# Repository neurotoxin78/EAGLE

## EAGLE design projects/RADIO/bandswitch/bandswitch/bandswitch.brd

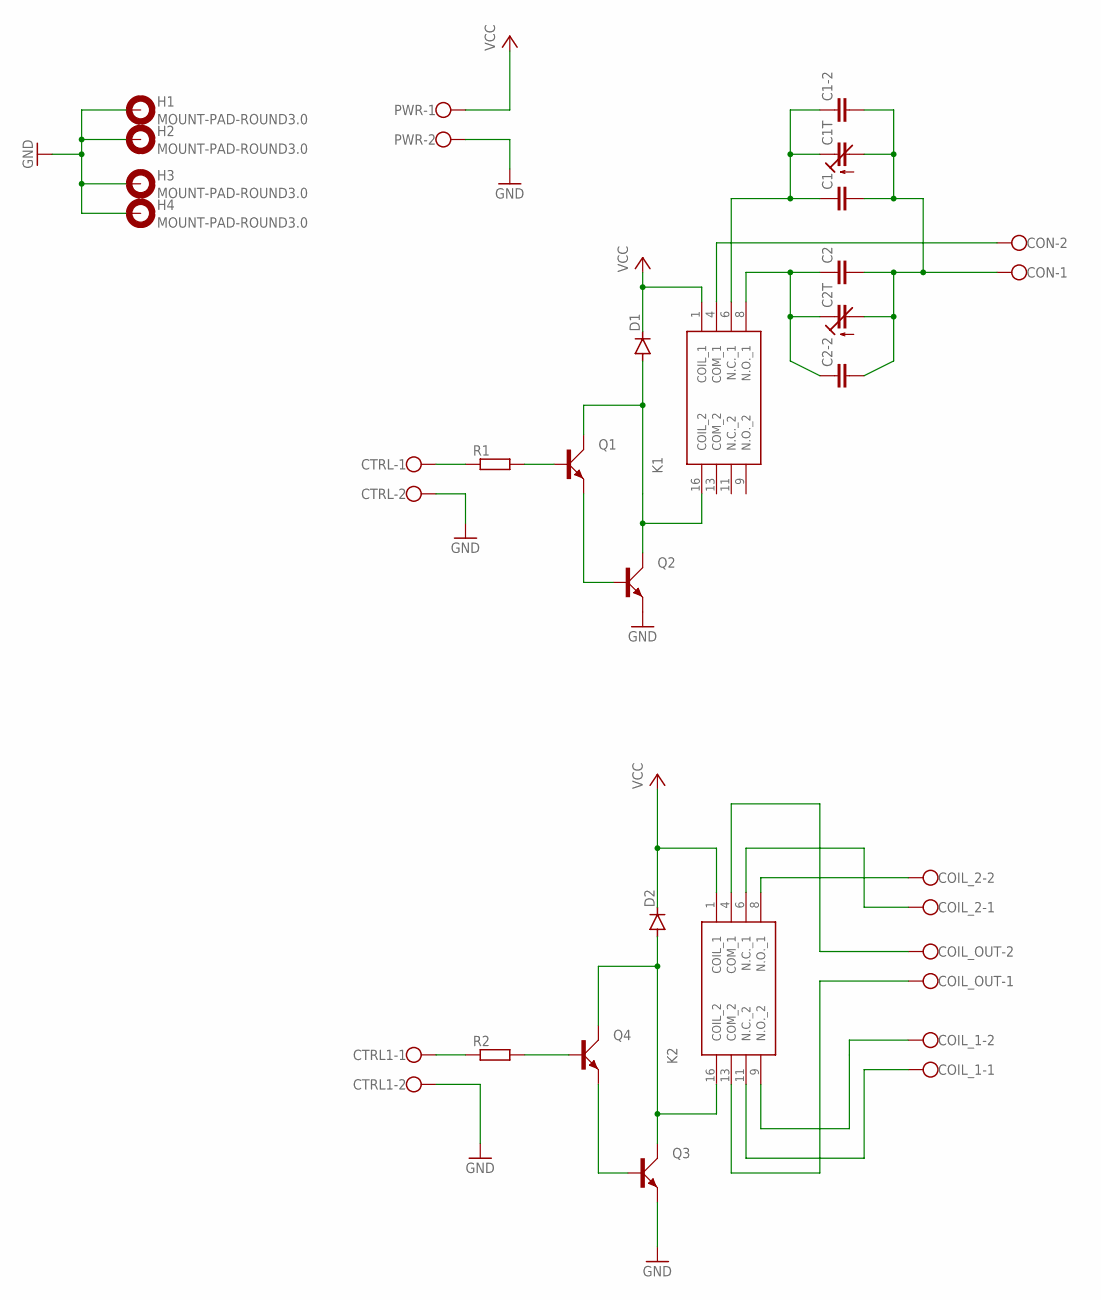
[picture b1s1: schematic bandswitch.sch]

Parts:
C1, C1-2, C2, C2-2: C_0805_PTH; C0805K
C1T, C2T: C_TRIM_TH; CTRIM3050.505
COIL_1, COIL_2: W237-102
COIL_OUT: W237-102
CON: W237-102
CTRL, CTRL1: W237-102
D1, D2: 1N4148DO35-7; DO35-7
H1, H2, H3, H4: MOUNT-PAD-ROUND3.0; 3,0-PAD
K1, K2: G5V-2-H1-DC5; G5V2H1DC5
PWR: W237-102
Q1, Q2, Q3, Q4: BC547; SOT54A
R1, R2: R_0805_PTH; R0805

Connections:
GND: CTRL.2, CTRL1.2, H1.B3,0, H2.B3,0, H3.B3,0, H4.B3,0, PWR.2, Q2.E, Q3.E
unnamed: Q1.E, Q2.B
unnamed: D1.A, K1.16 (COIL_2), Q1.C, Q2.C
unnamed: Q1.B, R1.2, R1.P$2 (2)
unnamed: CTRL.1, R1.1, R1.P$1 (1)
unnamed: D2.A, K2.16 (COIL_2), Q3.C, Q4.C
unnamed: Q3.B, Q4.E
unnamed: Q4.B, R2.2, R2.P$2 (2)
unnamed: CTRL1.1, R2.1, R2.P$1 (1)
unnamed: COIL_OUT.2, K2.4 (COM_1)
unnamed: C1.1, C1.P$1 (1), C1-2.1, C1-2.P$1 (1), C1T.2 (E), K1.6 (N.C._1)
unnamed: C2.1, C2.P$1 (1), C2-2.1, C2-2.P$1 (1), C2T.2 (E), K1.8 (N.O._1)
unnamed: C1.2, C1.P$2 (2), C1-2.2, C1-2.P$2 (2), C1T.1 (A), C2.2, C2.P$2 (2), C2-2.2, C2-2.P$2 (2), C2T.1 (A), CON.1
unnamed: CON.2, K1.4 (COM_1)
unnamed: COIL_OUT.1, K2.13 (COM_2)
unnamed: COIL_1.1, K2.11 (N.C._2)
unnamed: COIL_2.1, K2.6 (N.C._1)
unnamed: COIL_2.2, K2.8 (N.O._1)
unnamed: COIL_1.2, K2.9 (N.O._2)
VCC: D1.C, D2.C, K1.1 (COIL_1), K2.1 (COIL_1), PWR.1

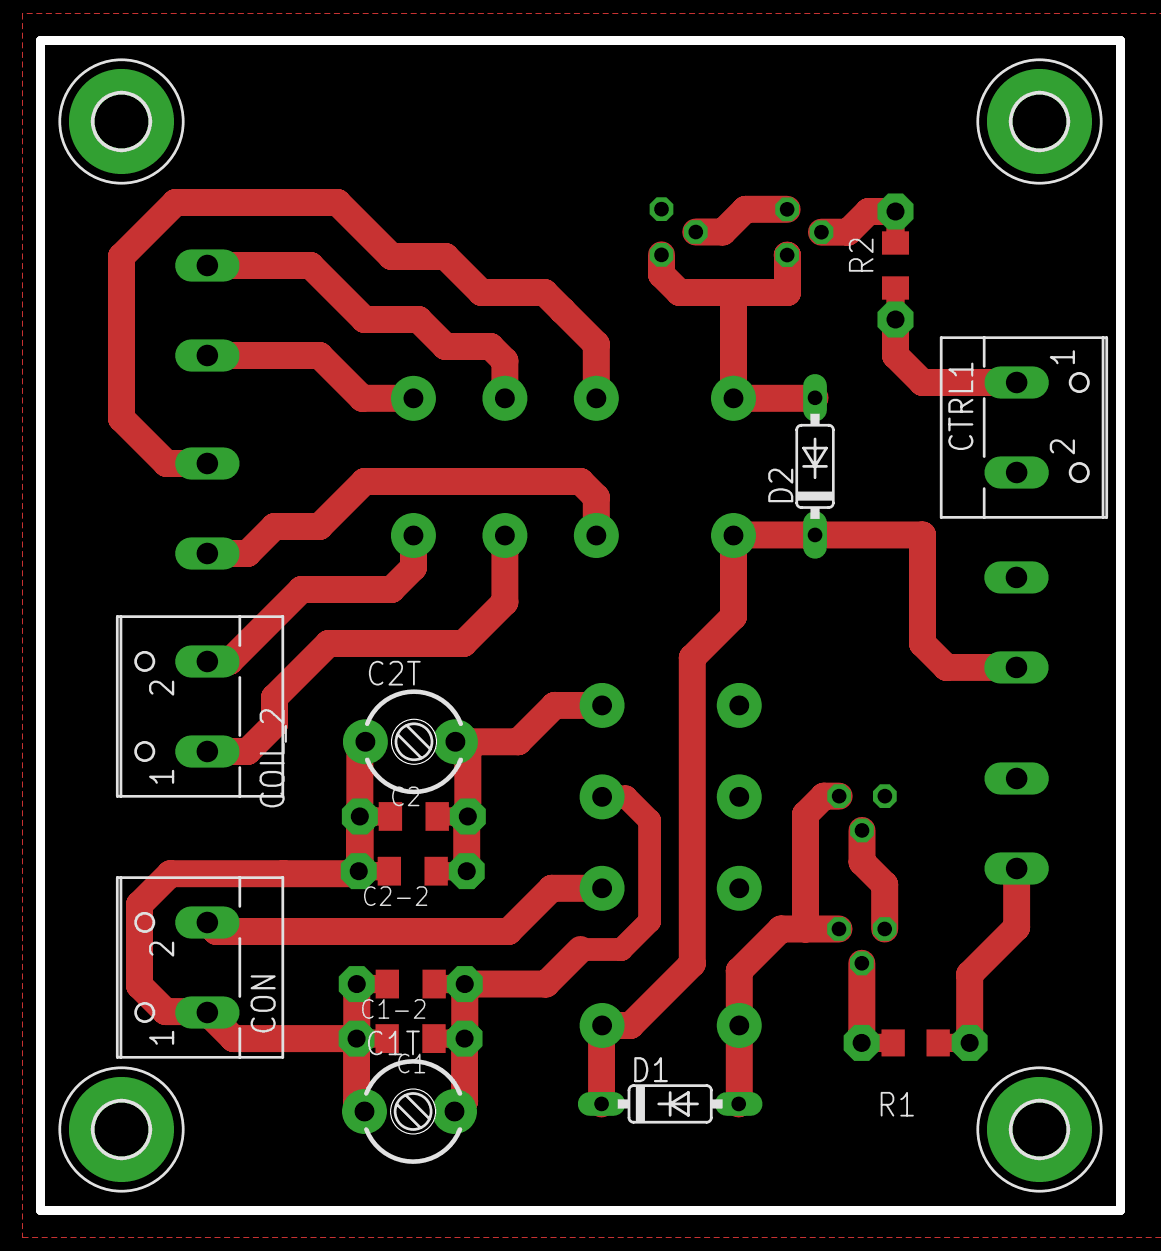
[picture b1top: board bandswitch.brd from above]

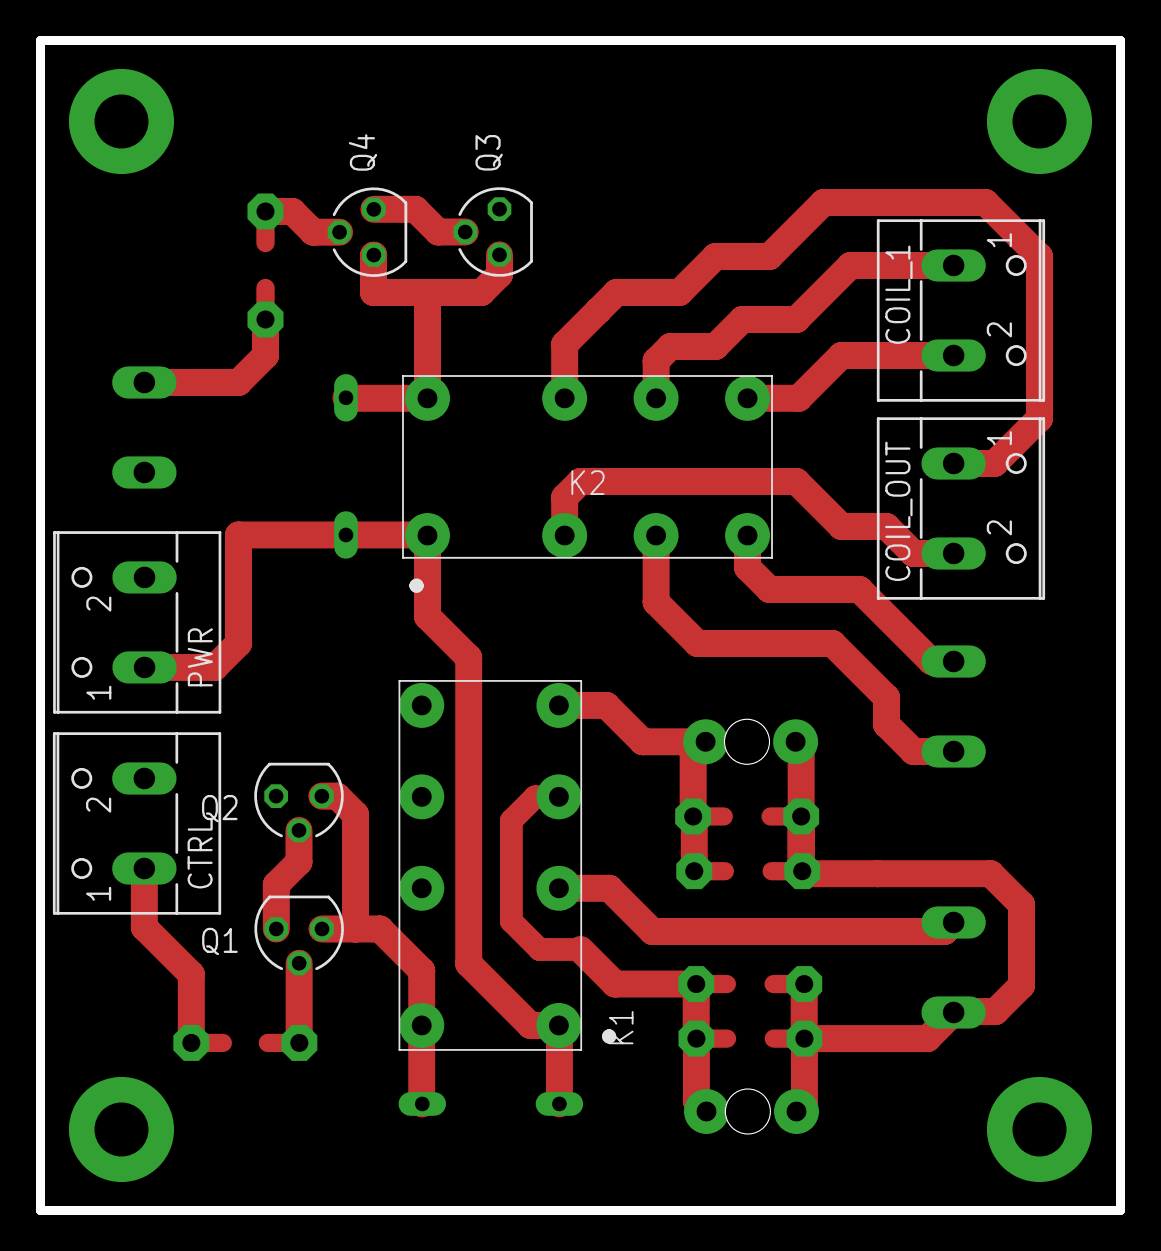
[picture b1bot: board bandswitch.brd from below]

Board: 2 copper layers, 60.0 x 65.0 mm, 27 parts (10 on the bottom side), 20 nets.

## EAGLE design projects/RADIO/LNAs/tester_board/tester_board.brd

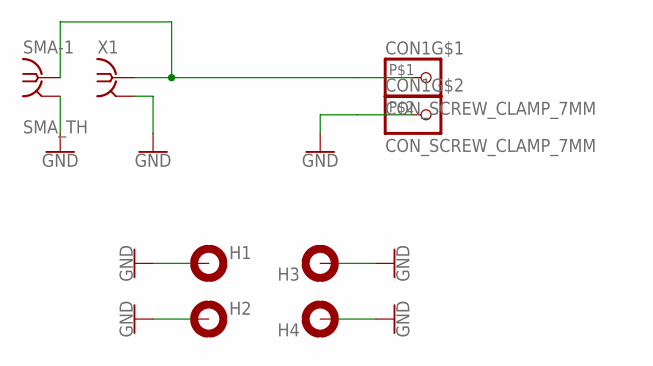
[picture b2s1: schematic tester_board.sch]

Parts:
CON1: CON_SCREW_CLAMP_7MM
H1, H2, H3, H4: MOUNT-PAD-ROUND3.0; 3,0-PAD
SMA-1: SMA_TH; BU-SMA-V
X1: SMA-142-0711-821/826; J502-ND-142-0711-821/826

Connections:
GND: CON1.P$2, H1.B3,0, H2.B3,0, H3.B3,0, H4.B3,0, SMA-1.2 (GND), SMA-1.3 (GND), SMA-1.4 (GND), SMA-1.5 (GND), X1.G@1 (2), X1.G@2 (2), X1.G@3 (2), X1.G@4 (2)
unnamed: CON1.P$1, SMA-1.1, X1.1

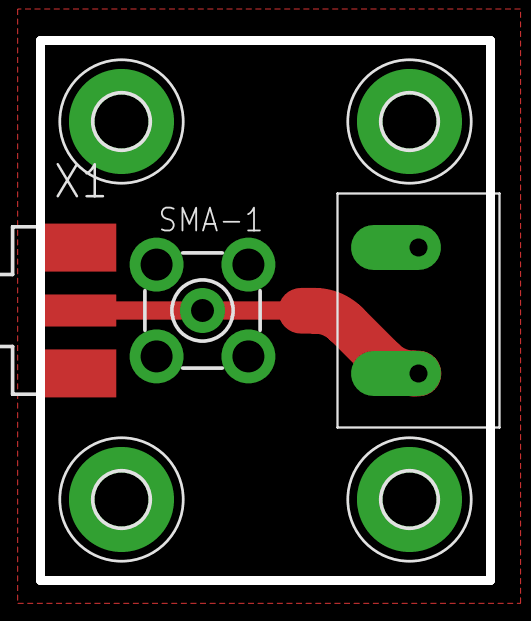
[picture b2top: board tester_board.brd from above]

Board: 2 copper layers, 25.0 x 30.0 mm, 7 parts (0 on the bottom side), 2 nets.

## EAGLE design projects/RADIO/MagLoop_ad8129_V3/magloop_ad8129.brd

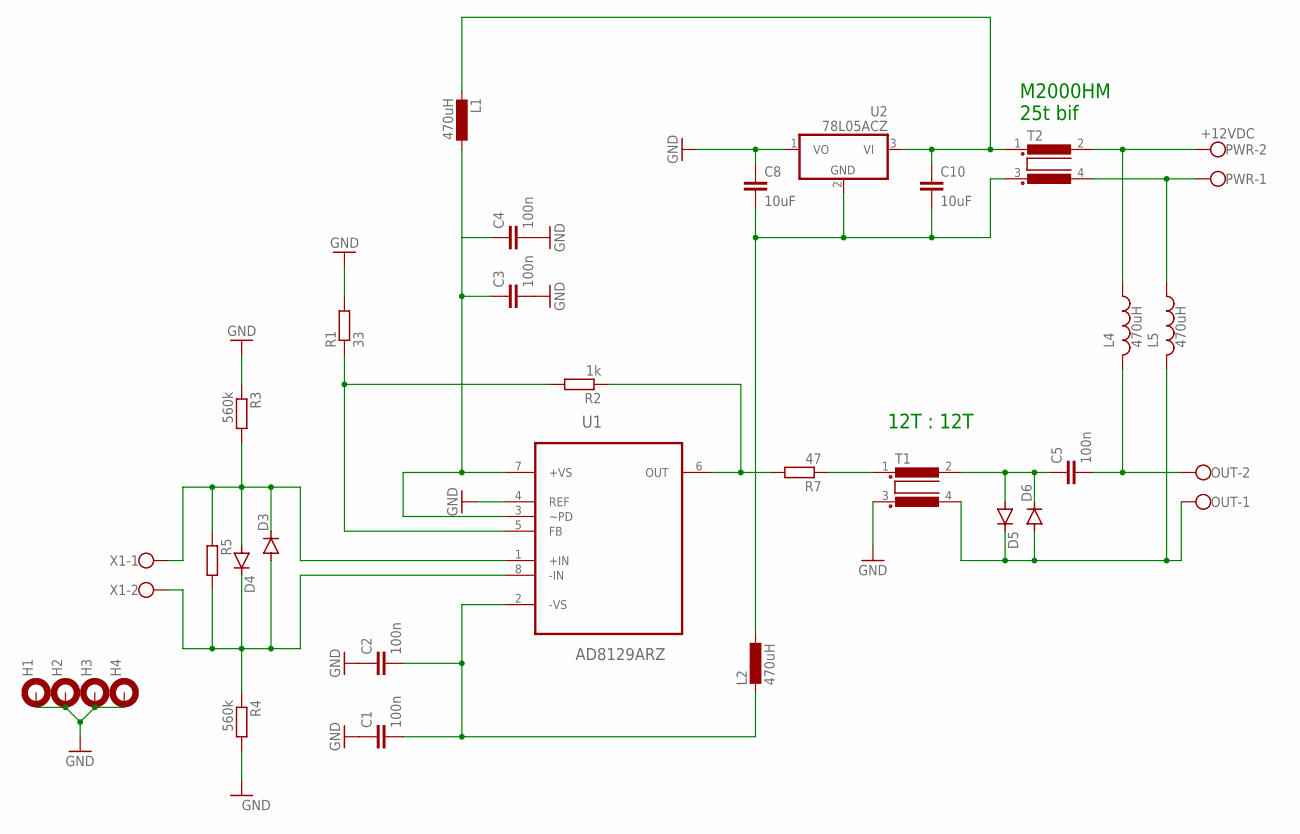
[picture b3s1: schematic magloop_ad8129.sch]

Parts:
C1, C2, C3, C4: 100n; C0805
C5: 100n; C0805K
C8, C10: 10uF; C1206K
D3, D4: LL4148; SOD-123_MINI-SMA
D5, D6: CGRM4001-G; SOD-123_MINI-SMA
H1, H2, H3, H4: MOUNT-PAD-ROUND3.0; 3,0-PAD
L1, L2: 470uH; 0207/10
L4, L5: 470uH; M0805
OUT: W237-102
PWR: +12VDC; W237-102
R1: 33; R0805W
R2: 1k; R0805W
R3, R4: 560k; R0805
R5: R_0805_PTH; R0805
R7: 47; R1206
T1, T2: R1405UB1/2; B1/2
U1: AD8129ARZ; SOIC127P600X175-8N
U2: 78L05ACZ; TO-92
X1: W237-102

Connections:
GND: C1.1, C2.1, C3.2, C4.2, C8.1, H1.B3,0, H2.B3,0, H3.B3,0, H4.B3,0, R1.2, R3.1, R3.P$1 (1), R4.2, R4.P$2 (2), T1.3, U1.4 (REF), U2.1 (VO)
unnamed: D3.C, D4.A, R3.2, R3.P$2 (2), R5.1, R5.P$1 (1), U1.1 (+IN), X1.1
unnamed: D3.A, D4.C, R4.1, R4.P$1 (1), R5.2, R5.P$2 (2), U1.8 (-IN), X1.2
unnamed: R1.1, R2.2, U1.5 (FB)
unnamed: R2.1, R7.2, U1.6 (OUT)
unnamed: C3.1, C4.1, L1.1, U1.3 (~PD), U1.7 (+VS)
unnamed: C10.1, L1.2, T2.1, U2.3 (VI)
unnamed: C8.2, C10.2, L2.1, T2.3, U2.2 (GND)
unnamed: L5.1, L5.P$1 (1), PWR.1, T2.4
unnamed: L4.1, L4.P$1 (1), PWR.2, T2.2
unnamed: C1.2, C2.2, L2.2, U1.2 (-VS)
unnamed: R7.1, T1.1
unnamed: C5.1, C5.P$1 (1), D5.A, D6.C, T1.2
unnamed: C5.2, C5.P$2 (2), L4.2, L4.P$2 (2), OUT.2
unnamed: D5.C, D6.A, L5.2, L5.P$2 (2), OUT.1, T1.4

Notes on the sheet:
12T : 12T
M2000HM 25t bif

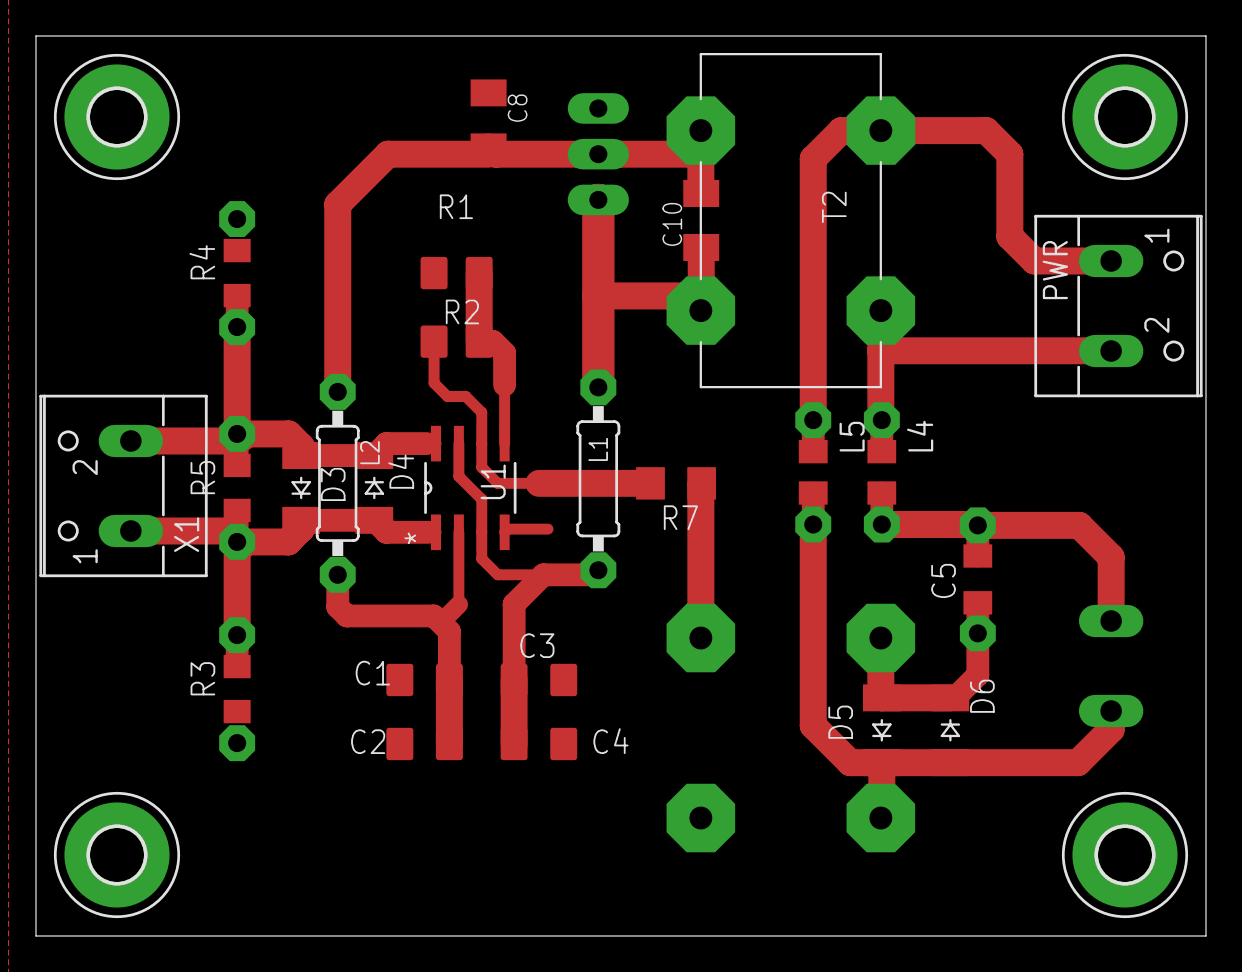
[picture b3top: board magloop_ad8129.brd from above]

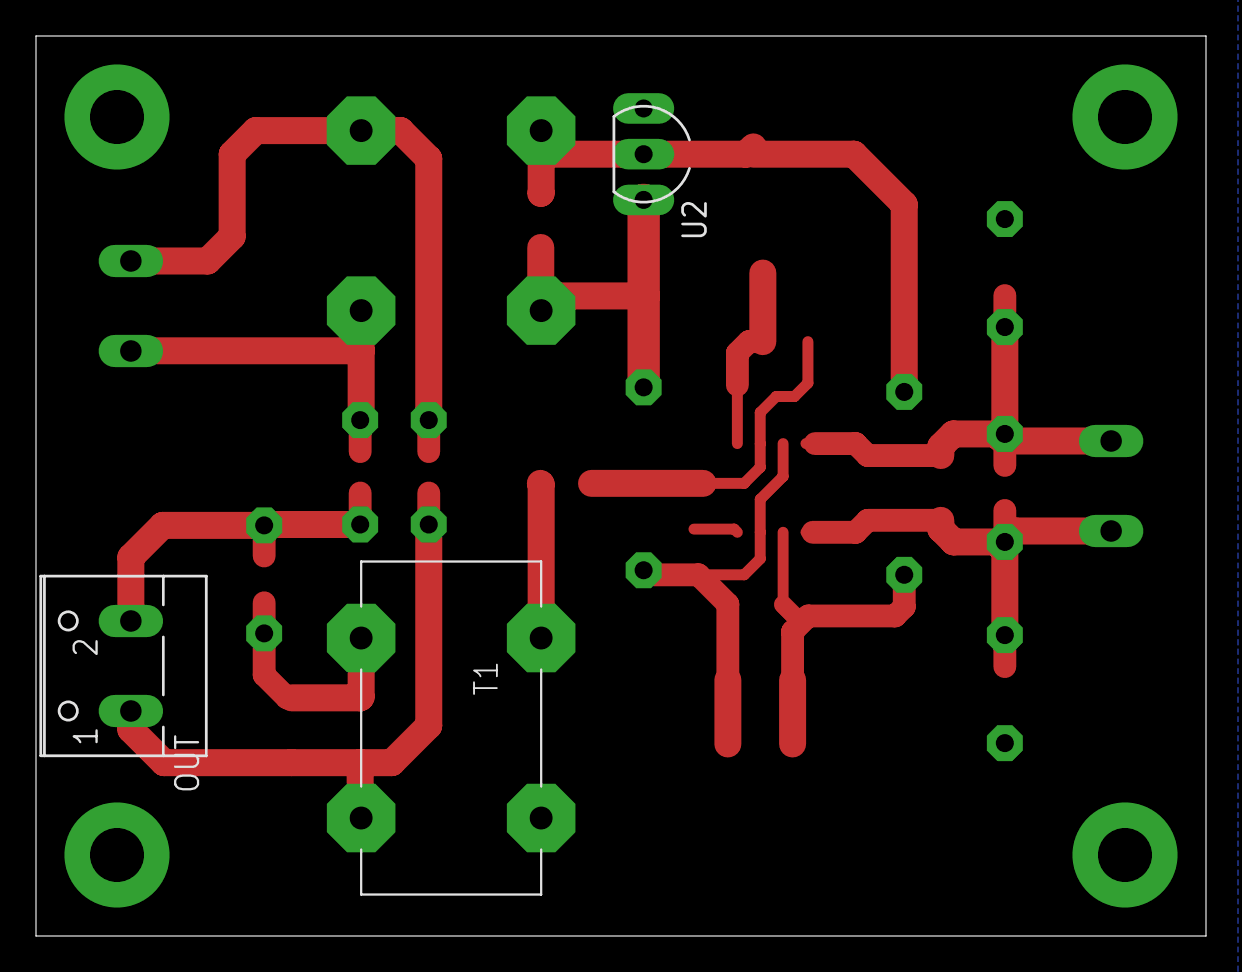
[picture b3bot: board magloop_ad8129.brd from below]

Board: 2 copper layers, 65.0 x 50.0 mm, 32 parts (3 on the bottom side), 15 nets.

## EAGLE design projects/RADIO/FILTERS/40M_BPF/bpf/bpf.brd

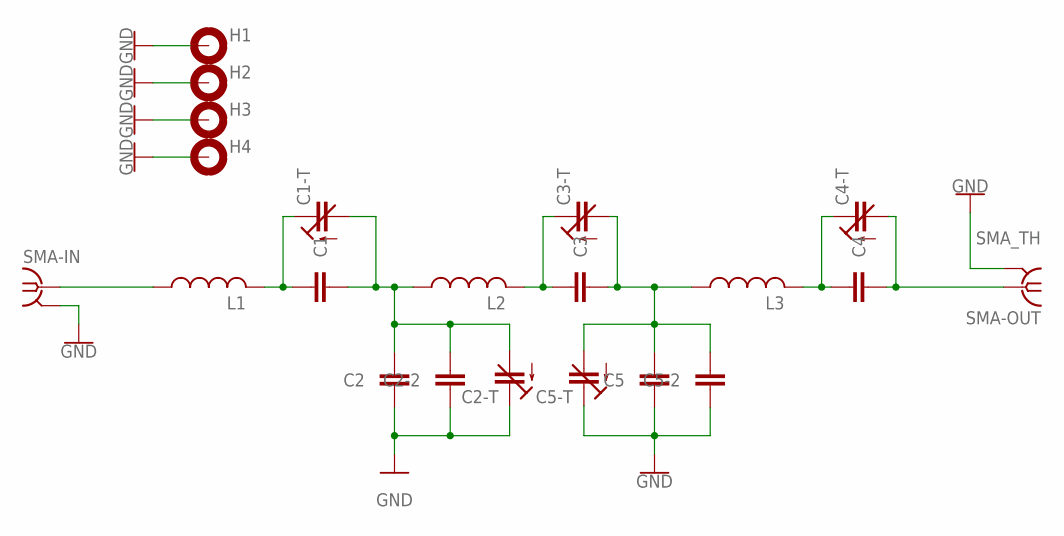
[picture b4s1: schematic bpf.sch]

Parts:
C1, C2, C2-2, C3, C4, C5, C5-2: C_0805_PTH; C0805K
C1-T, C2-T, C3-T, C4-T, C5-T: C_TRIM_TH; CTRIM3050.505
H1, H2, H3, H4: MOUNT-PAD-ROUND3.0; 3,0-PAD
L1, L2, L3: L_0805_PTH; M0805
SMA-IN: SMA-142-0711-821/826; J502-ND-142-0711-821/826
SMA-OUT: SMA_TH; BU-SMA-V

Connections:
GND: C2.1, C2.P$1 (1), C2-2.1, C2-2.P$1 (1), C2-T.2 (E), C5.1, C5.P$1 (1), C5-2.1, C5-2.P$1 (1), C5-T.2 (E), H1.B3,0, H2.B3,0, H3.B3,0, H4.B3,0, SMA-IN.G@1 (2), SMA-IN.G@2 (2), SMA-IN.G@3 (2), SMA-IN.G@4 (2), SMA-OUT.2 (GND), SMA-OUT.3 (GND), SMA-OUT.4 (GND), SMA-OUT.5 (GND)
unnamed: L1.1, L1.P$1 (1), SMA-IN.1
unnamed: C1.1, C1.P$1 (1), C1-T.2 (E), L1.2, L1.P$2 (2)
unnamed: C1.2, C1.P$2 (2), C1-T.1 (A), C2.2, C2.P$2 (2), C2-2.2, C2-2.P$2 (2), C2-T.1 (A), L2.1, L2.P$1 (1)
unnamed: C3.1, C3.P$1 (1), C3-T.2 (E), L2.2, L2.P$2 (2)
unnamed: C3.2, C3.P$2 (2), C3-T.1 (A), C5.2, C5.P$2 (2), C5-2.2, C5-2.P$2 (2), C5-T.1 (A), L3.1, L3.P$1 (1)
unnamed: C4.1, C4.P$1 (1), C4-T.2 (E), L3.2, L3.P$2 (2)
unnamed: C4.2, C4.P$2 (2), C4-T.1 (A), SMA-OUT.1

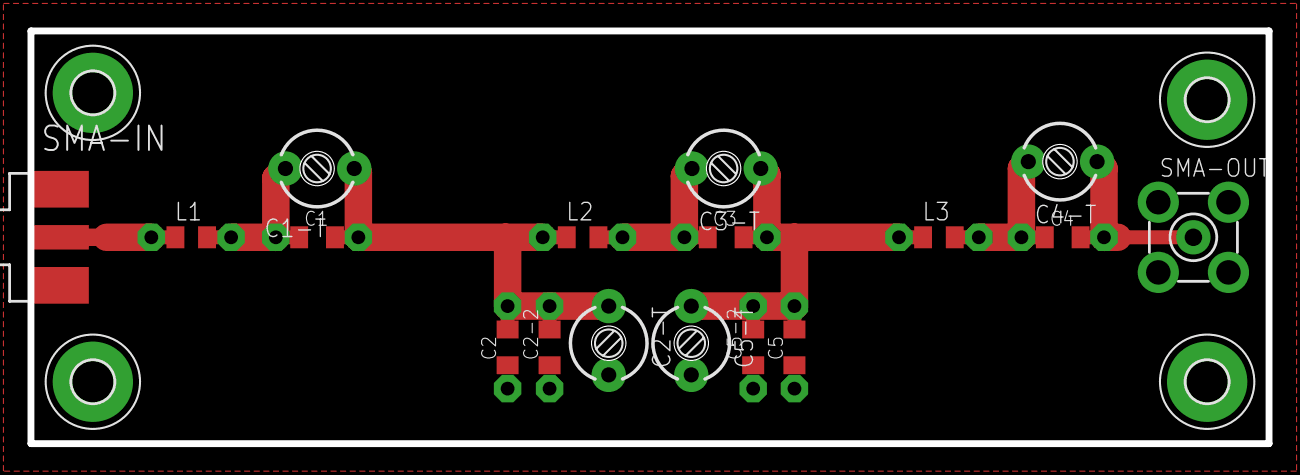
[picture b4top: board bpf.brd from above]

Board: 2 copper layers, 90.0 x 30.0 mm, 21 parts (0 on the bottom side), 8 nets.

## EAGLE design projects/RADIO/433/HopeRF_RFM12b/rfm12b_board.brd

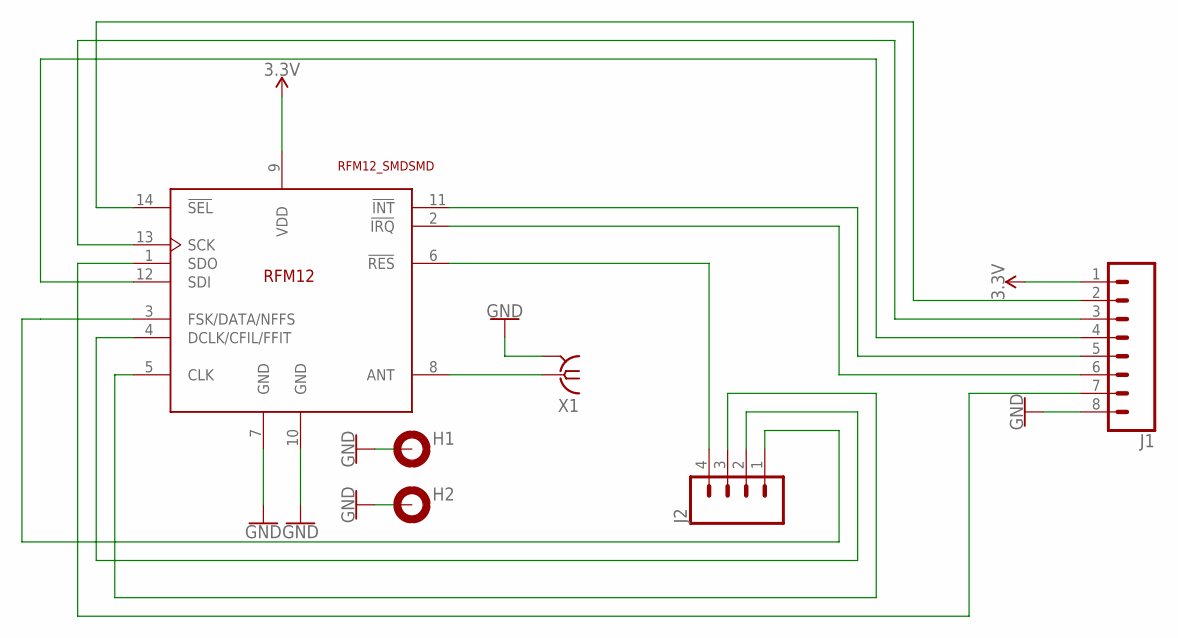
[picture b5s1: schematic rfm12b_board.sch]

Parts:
H1, H2: MOUNT-PAD-ROUND3.0; 3,0-PAD
J1: CONN_08LONGPADS; 1X08_LONGPADS
J2: CONN_04JST-PTH-VERT; JST-4-PTH-VERT
U$1: RFM12_SMDSMD; RFM12
X1: SMA-142-0711-821/826; J502-ND-142-0711-821/826

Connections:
3.3V: J1.1, U$1.9 (VDD)
GND: H1.B3,0, H2.B3,0, J1.8, U$1.7 (GND), U$1.10 (GND), X1.G@1 (2), X1.G@2 (2), X1.G@3 (2), X1.G@4 (2)
unnamed: U$1.8 (ANT), X1.1
unnamed: J1.2, U$1.14 (!SEL)
unnamed: J1.3, U$1.13 (SCK)
unnamed: J1.4, U$1.12 (SDI)
unnamed: J1.5, U$1.11 (!INT)
unnamed: J1.6, U$1.2 (!IRQ)
unnamed: J1.7, U$1.1 (SDO)
unnamed: J2.4, U$1.6 (!RES)
unnamed: J2.3, U$1.5 (CLK)
unnamed: J2.2, U$1.4 (DCLK/CFIL/FFIT)
unnamed: J2.1, U$1.3 (FSK/DATA/NFFS)

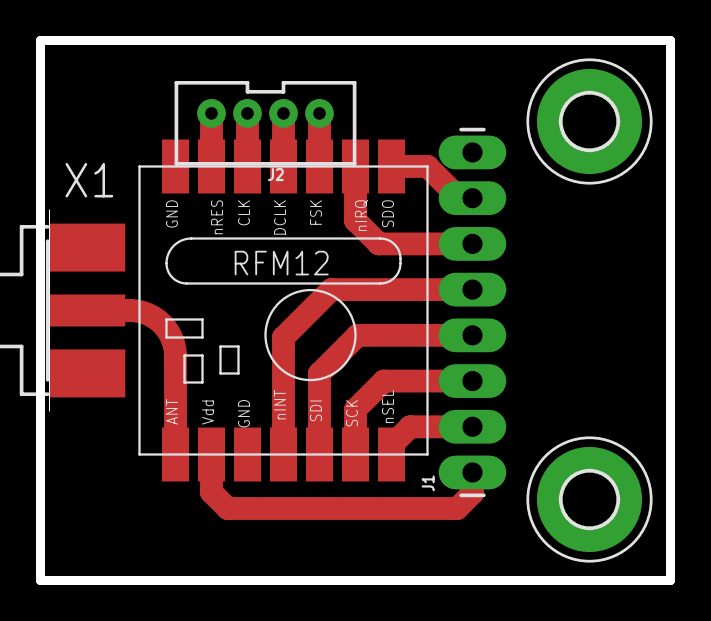
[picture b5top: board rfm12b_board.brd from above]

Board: 2 copper layers, 35.0 x 30.0 mm, 6 parts (0 on the bottom side), 13 nets.

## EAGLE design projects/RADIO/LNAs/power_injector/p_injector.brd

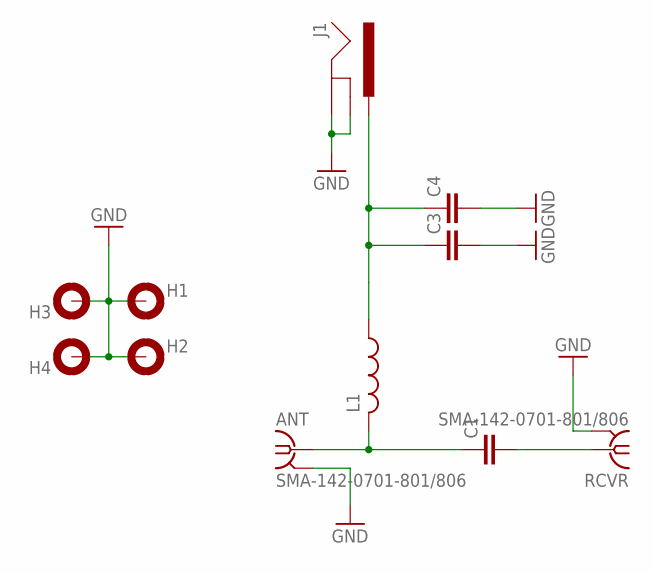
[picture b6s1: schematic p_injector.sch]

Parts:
ANT: SMA-142-0701-801/806; J502-ND-142-0701-801/806
C1: C_0805_PTH; C0805K
C3, C4: C_0805_SMD; C0805
H1, H2, H3, H4: MOUNT-PAD-ROUND3.0; 3,0-PAD
J1: POWER_JACKPOWER_JACK_SLOT; POWER_JACK_PTH_SLOT
L1: L_0805_PTH; M0805
RCVR: SMA-142-0701-801/806; J502-ND-142-0701-801/806

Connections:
GND: ANT.G@1 (2), ANT.G@2 (2), ANT.G@3 (2), ANT.G@4 (2), C3.2, C4.2, H1.B3,0, H2.B3,0, H3.B3,0, H4.B3,0, J1.GND, J1.GNDBREAK, RCVR.G@1 (2), RCVR.G@2 (2), RCVR.G@3 (2), RCVR.G@4 (2)
unnamed: ANT.1, C1.1, C1.P$1 (1), L1.2, L1.P$2 (2)
unnamed: C1.2, C1.P$2 (2), RCVR.1
unnamed: C3.1, C4.1, J1.PWR, L1.1, L1.P$1 (1)

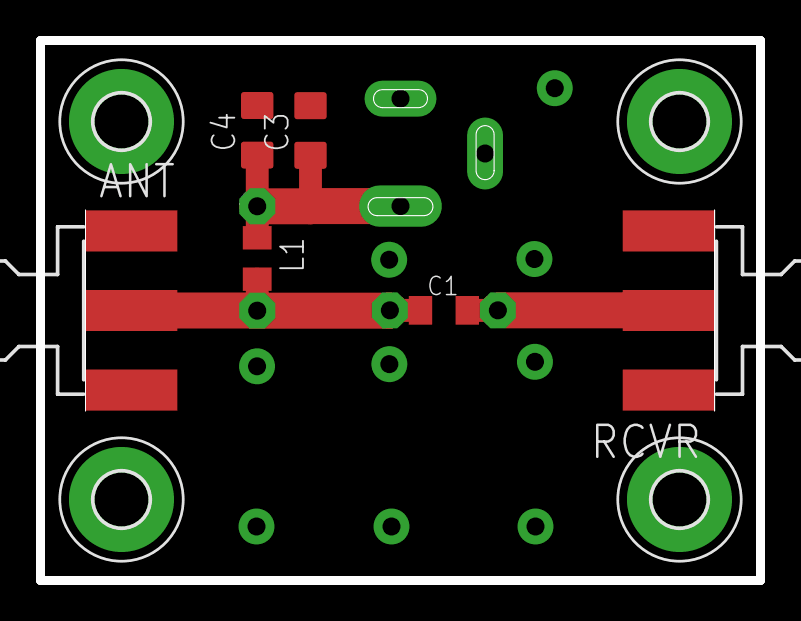
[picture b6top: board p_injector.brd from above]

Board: 2 copper layers, 40.0 x 30.0 mm, 11 parts (1 on the bottom side), 4 nets.

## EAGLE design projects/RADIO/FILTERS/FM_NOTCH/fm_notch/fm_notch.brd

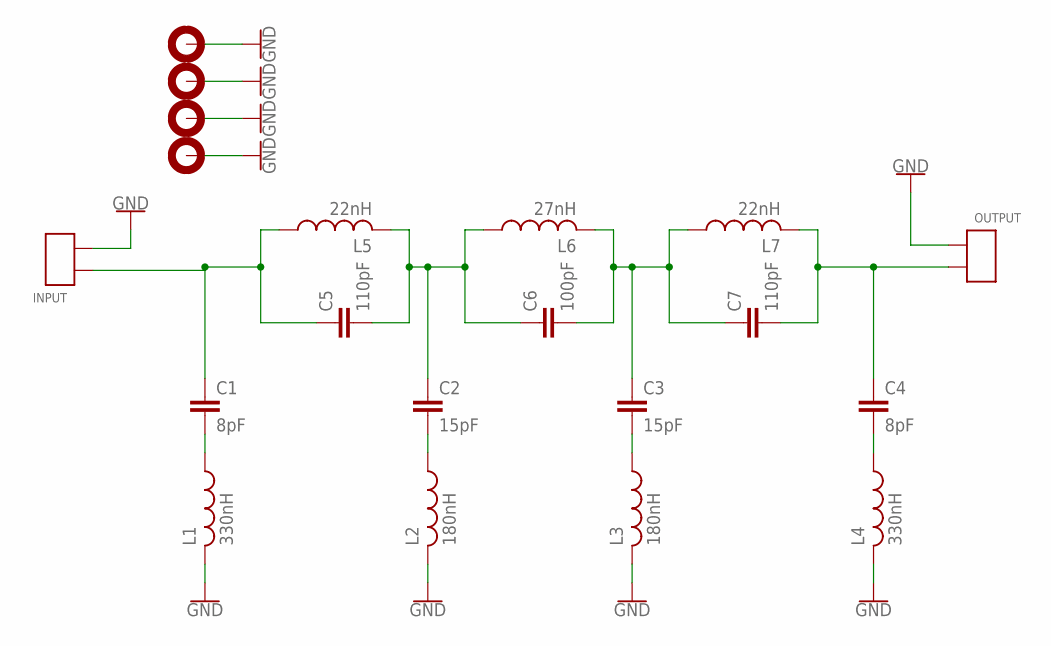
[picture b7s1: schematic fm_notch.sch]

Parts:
C1, C4: 8pF; C0805
C2, C3: 15pF; C0805
C5, C7: 110pF; C0805
C6: 100pF; C0805
H1, H2, H3, H4: MOUNT-PAD-ROUND3.0; 3,0-PAD
INPUT: INPUT; 2X_SMD_PTH
L1, L4: 330nH; C0805
L2, L3: 180nH; C0805
L5, L7: 22nH; C0805
L6: 27nH; C0805
OUTPUT: 2X_SMD_PTH_PIN; 2X_SMD_PTH

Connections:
GND: H1.B3,0, H2.B3,0, H3.B3,0, H4.B3,0, INPUT.P$2 (PIN1), INPUT.T$2 (PIN1), L1.2, L2.2, L3.2, L4.2, OUTPUT.P$1 (PIN0), OUTPUT.T$1 (PIN0)
unnamed: C1.1, C5.1, INPUT.P$1 (PIN0), INPUT.T$1 (PIN0), L5.1
unnamed: C2.2, L2.1
unnamed: C3.1, C6.2, C7.1, L6.2, L7.1
unnamed: C3.2, L3.1
unnamed: C4.1, C7.2, L7.2, OUTPUT.P$2 (PIN1), OUTPUT.T$2 (PIN1)
unnamed: C4.2, L4.1
unnamed: C2.1, C5.2, C6.1, L5.2, L6.1
unnamed: C1.2, L1.1

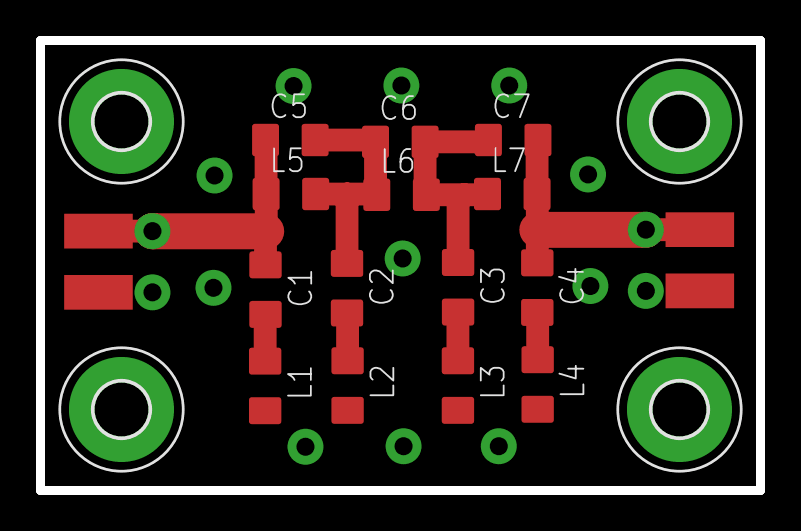
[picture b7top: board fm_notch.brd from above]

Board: 2 copper layers, 40.0 x 25.0 mm, 20 parts (0 on the bottom side), 9 nets.

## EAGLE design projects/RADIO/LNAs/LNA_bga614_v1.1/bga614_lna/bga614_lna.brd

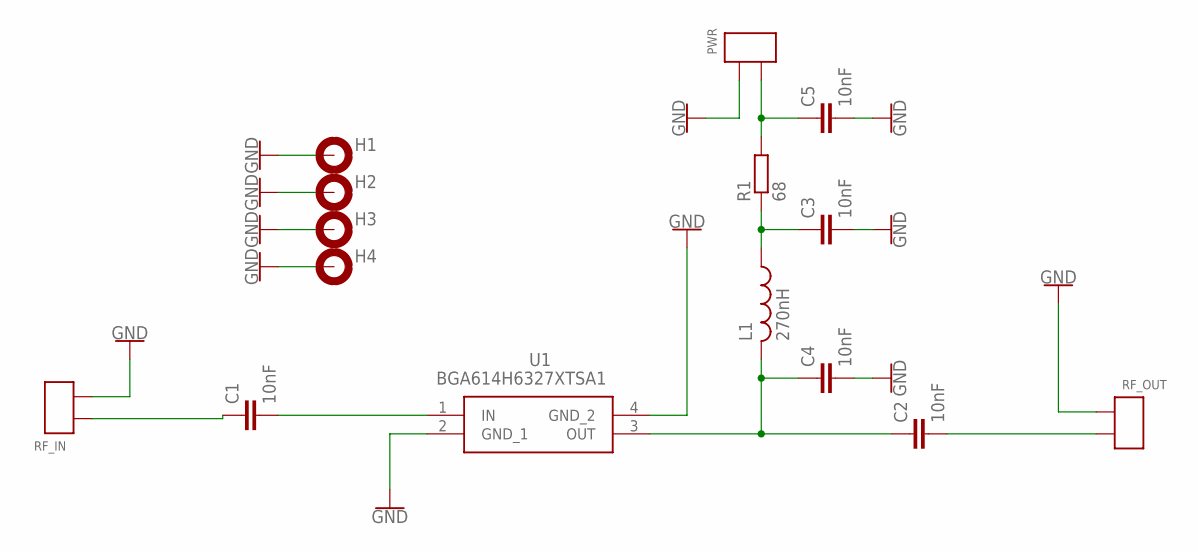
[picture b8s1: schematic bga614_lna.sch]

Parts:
C1, C2, C3, C4, C5: 10nF; C0805
H1, H2, H3, H4: MOUNT-PAD-ROUND3.0; 3,0-PAD
L1: 270nH; M0805
PWR: 2X_SMD_PTH_PIN; 2X_SMD_PTH
R1: 68; R0805W
RF_IN: 2X_SMD_PTH_PIN; 2X_SMD_PTH
RF_OUT: 2X_SMD_PTH_PIN; 2X_SMD_PTH
U1: BGA614H6327XTSA1

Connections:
GND: C3.2, C4.2, C5.2, H1.B3,0, H2.B3,0, H3.B3,0, H4.B3,0, PWR.P$1 (PIN0), PWR.T$1 (PIN0), RF_IN.P$2 (PIN1), RF_IN.T$2 (PIN1), RF_OUT.P$1 (PIN0), RF_OUT.T$1 (PIN0), U1.2 (GND_1), U1.4 (GND_2)
unnamed: C2.1, C4.1, L1.2, L1.P$2 (2), U1.3 (OUT)
unnamed: C3.1, L1.1, L1.P$1 (1), R1.1
unnamed: C5.1, PWR.P$2 (PIN1), PWR.T$2 (PIN1), R1.2
unnamed: C2.2, RF_OUT.P$2 (PIN1), RF_OUT.T$2 (PIN1)
unnamed: C1.2, U1.1 (IN)
unnamed: C1.1, RF_IN.P$1 (PIN0), RF_IN.T$1 (PIN0)

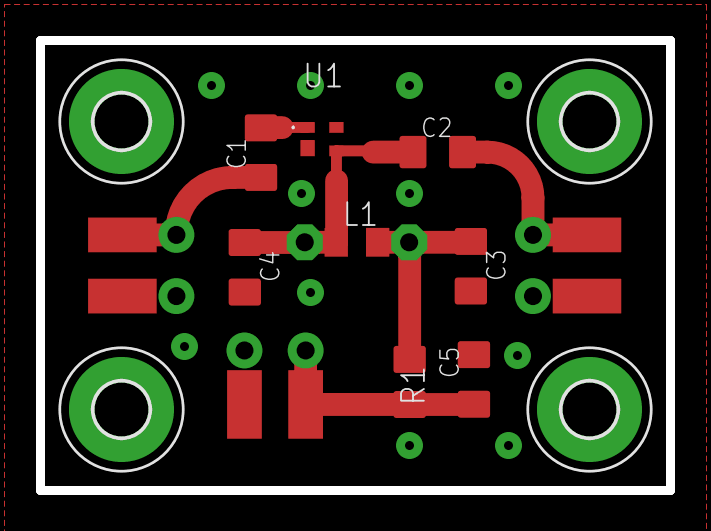
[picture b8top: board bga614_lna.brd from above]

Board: 2 copper layers, 35.0 x 25.0 mm, 15 parts (0 on the bottom side), 7 nets.

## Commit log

2022-05-02 My Eagle Projects
    Мої проекти в Eagle
2022-05-10 BackUp
2022-05-20 add new project
2022-05-27 add sa612_SW_receiver
2022-06-07 Update 07/06/2022
2022-06-07 update lib
2022-06-17 Upload

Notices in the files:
parts and their libraries:
SparkFun-Connectors: Licensing: Creative Commons ShareAlike 4.0 International - https://creativecommons.org/licenses/by-sa/4.0
